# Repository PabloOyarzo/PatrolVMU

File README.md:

# PatrolVMU
Vehicle Monitoring Unit

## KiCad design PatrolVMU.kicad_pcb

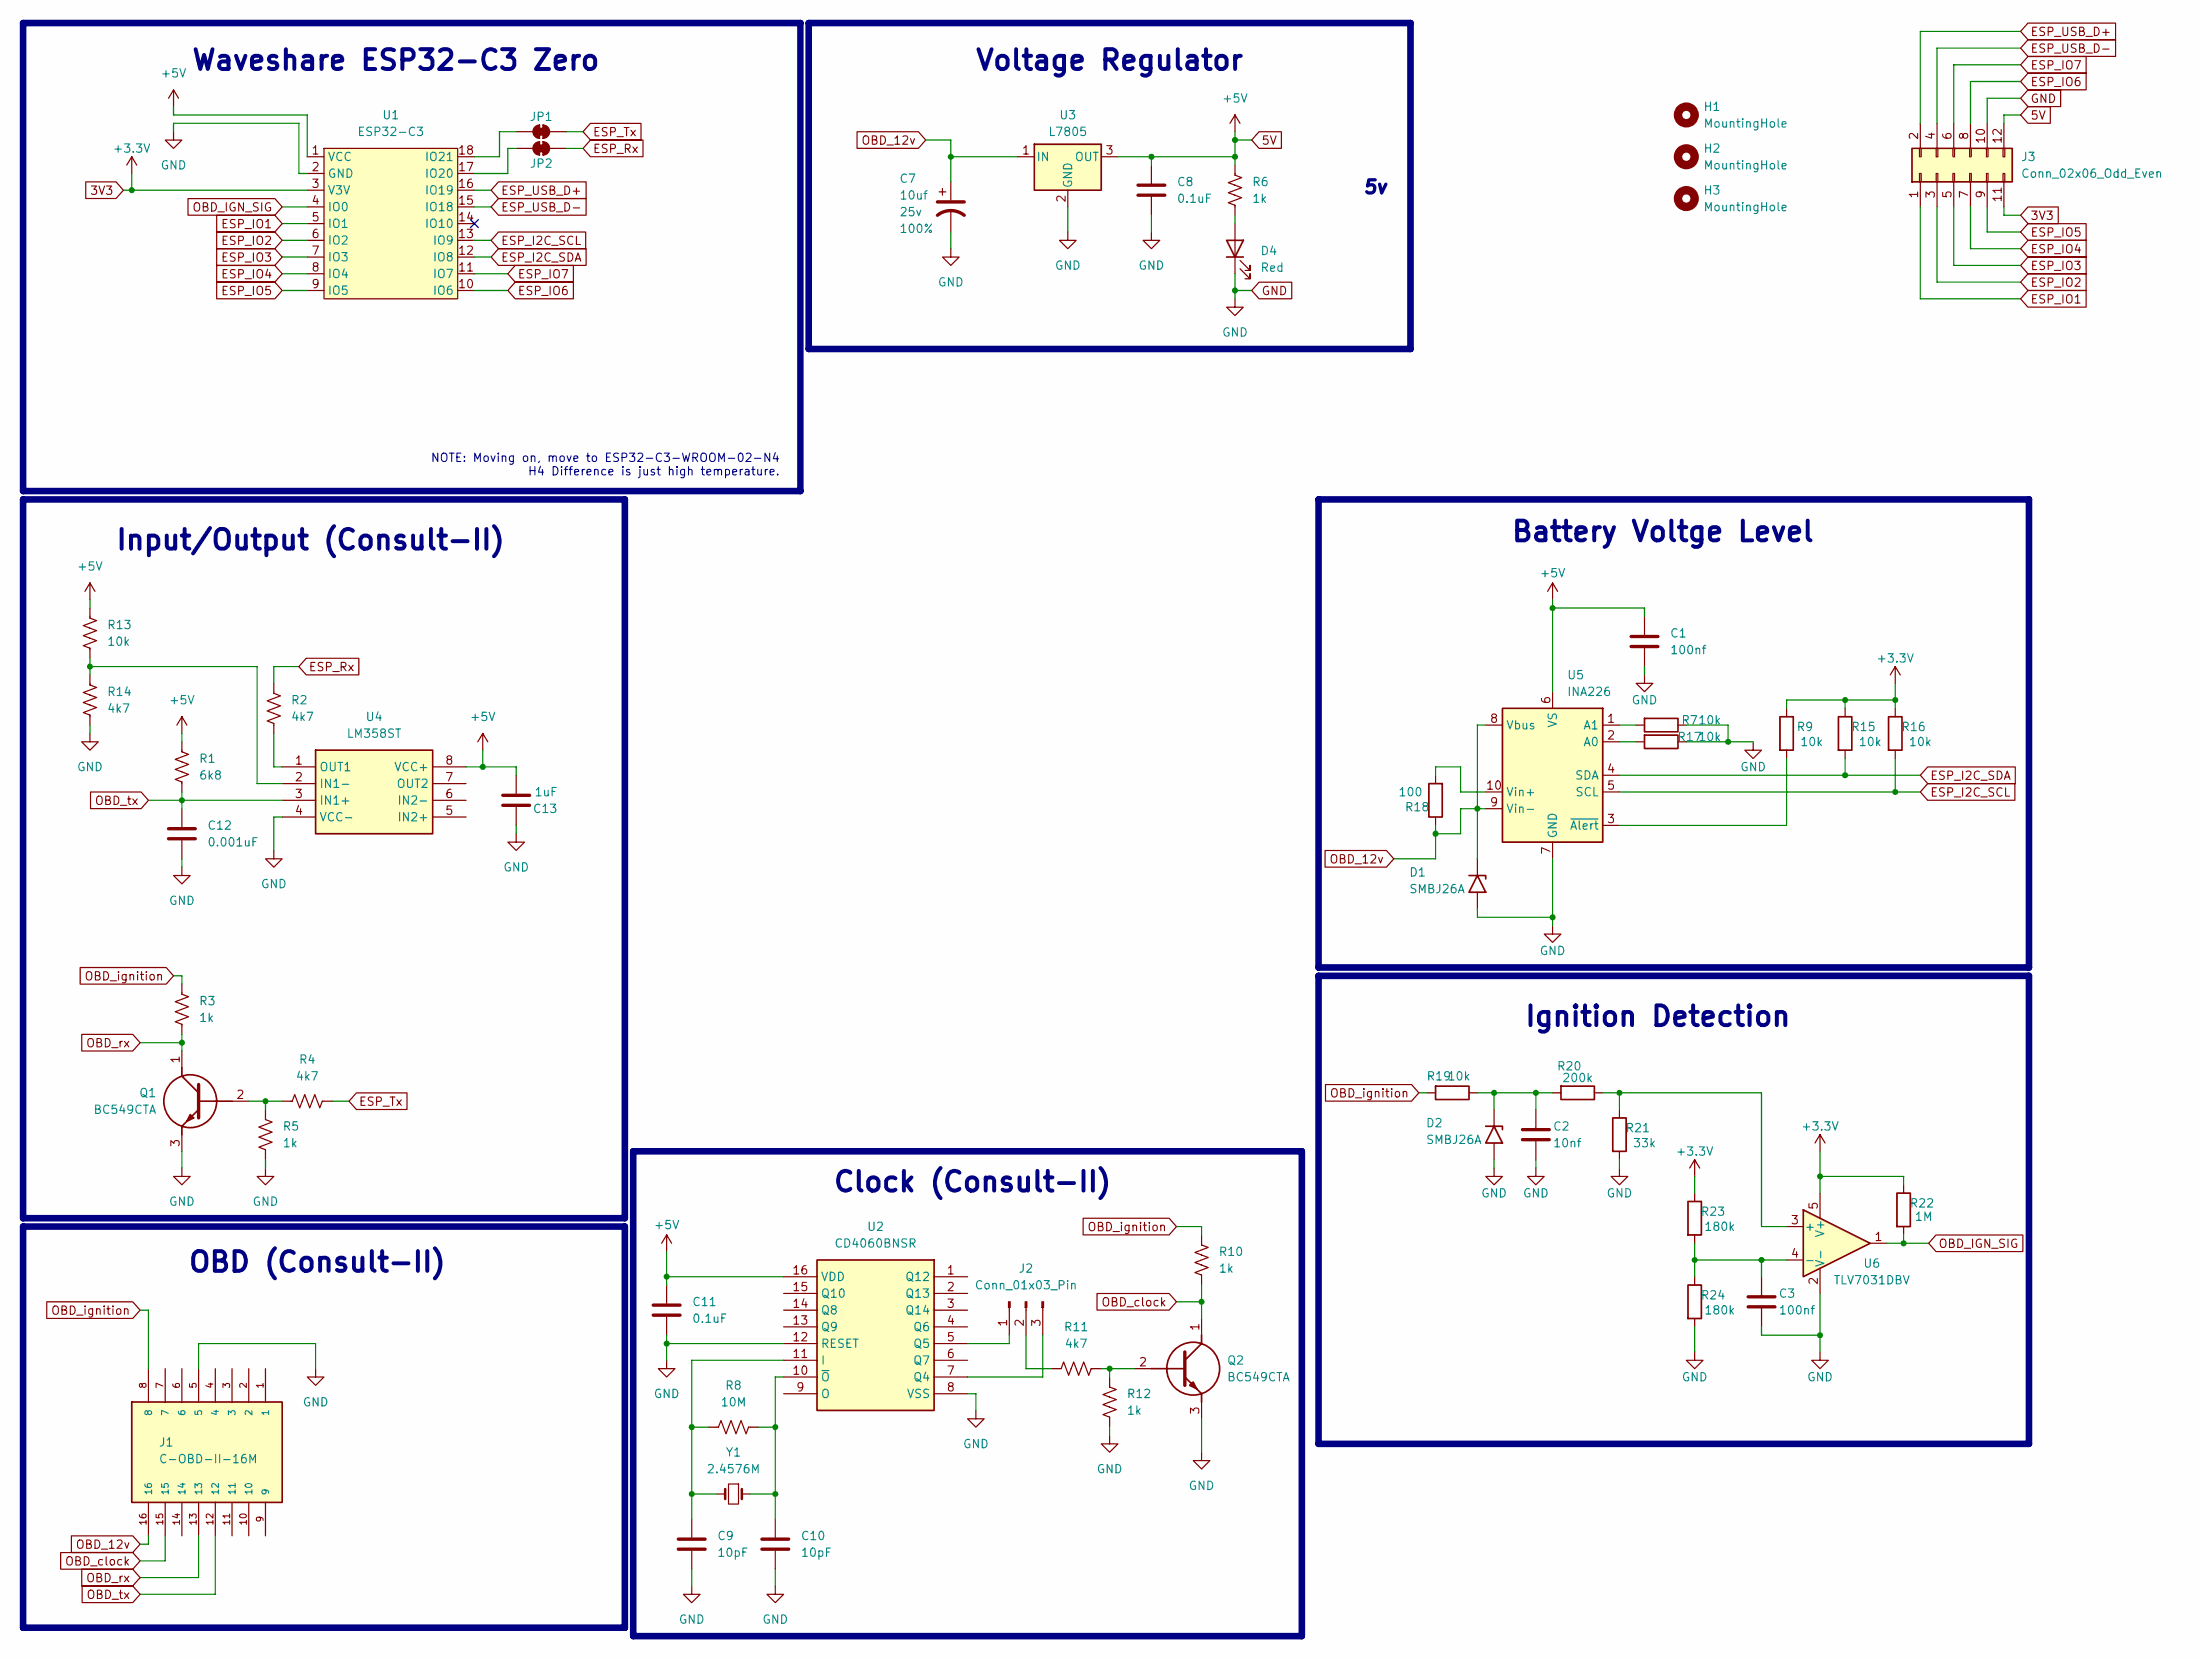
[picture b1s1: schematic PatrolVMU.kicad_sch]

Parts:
C1, C3: 100nf; C_0805_2012Metric
C2: 10nf; C_0805_2012Metric
C7: 10uf; C_0805_2012Metric; Voltage 25v; Tolerance 100%
C8, C11: 0.1uF; C_0805_2012Metric
C9, C10: 10pF; C_0805_2012Metric
C12: 0.001uF; C_0805_2012Metric
C13: 1uF; C_0805_2012Metric
D1, D2: SMBJ26A; D_SMB
D4: Red; LED_0805_2012Metric
H1, H2, H3: MountingHole; MountingHole_2.2mm_M2
J1: C-OBD-II-16M; COMTECH_C-OBD-II-16M; PARTREV A
J2: Conn_01x03_Pin; SolderJumper-3_P1.3mm_Bridged2Bar12_Pad1.0x1.5mm
J3: Conn_02x06_Odd_Even; PinHeader_2x06_P2.54mm_Vertical
JP1, JP2: SolderJumper_2_Bridged; SolderJumper-2_P1.3mm_Bridged2Bar_Pad1.0x1.5mm
Q1, Q2: BC549CTA; BC33740TA; Mouser Part Number 512-BC549CTA
R1: 6k8; C_0805_2012Metric
R2, R4, R11, R14: 4k7; C_0805_2012Metric
R3, R5, R6, R10, R12: 1k; C_0805_2012Metric
R7, R9, R13, R15, R16, R17, R19: 10k; C_0805_2012Metric
R8: 10M; C_0805_2012Metric
R18: 100; R_2512_6332Metric
R20: 200k; C_0805_2012Metric
R21: 33k; C_0805_2012Metric
R22: 1M; C_0805_2012Metric
R23, R24: 180k; C_0805_2012Metric
U1: ESP32-C3; Waveshare-ESP32-C3-Zero
U2: CD4060BNSR; SOIC127P780X200-16N; Mouser Part Number 595-CD4060BNSR
U3: L7805; TO-263-2
U4: LM358ST; SOP65P490X110-8N; Mouser Part Number 511-LM358S
U5: INA226; VSSOP-10_3x3mm_P0.5mm
U6: TLV7031DBV; SOT-23-5
Y1: 2.4576M; Crystal_HC49-4H_Vertical

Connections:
3V3: J3.11, R9.1, R15.1, R16.1, R22.1, R23.1, U1.3 (V3V), U6.5 (V+)
5V: C1.1, C8.1, C11.1, C13.2, J3.12, R1.1, R6.1, R13.1, U1.1 (VCC), U2.16 (VDD), U3.3 (OUT), U4.8 (VCC+), U5.6 (VS)
ESP_I2C_SCL: R16.2, U1.13 (IO9), U5.5 (SCL)
ESP_I2C_SDA: R15.2, U1.12 (IO8), U5.4 (SDA)
ESP_IO1: J3.1, U1.5 (IO1)
ESP_IO2: J3.3, U1.6 (IO2)
ESP_IO3: J3.5, U1.7 (IO3)
ESP_IO4: J3.7, U1.8 (IO4)
ESP_IO5: J3.9, U1.9 (IO5)
ESP_IO6: J3.8, U1.10 (IO6)
ESP_IO7: J3.6, U1.11 (IO7)
ESP_Rx: JP2.2 (B), R2.1
ESP_Tx: JP1.2 (B), R4.2
ESP_USB_D+: J3.2, U1.16 (IO19)
ESP_USB_D-: J3.4, U1.15 (IO18)
GND: C1.2, C2.2, C3.2, C7.2, C8.2, C9.2, C10.2, C11.2, C12.2, C13.1, D1.2 (A2), D2.2 (A2), D4.1 (K), J1.5, J3.10, Q1.3 (E), Q2.3 (E), R5.2, R7.1, R12.2, R14.2, R17.1, R21.2, R24.2, U1.2 (GND), U2.8 (VSS), U2.12 (RESET), U3.2 (GND), U4.4 (VCC-), U5.7 (GND), U6.2 (V-)
unnamed: C2.1, D2.1 (A1), R19.1, R20.2
unnamed: D4.2 (A), R6.2
unnamed: J2.1, U2.5 (Q5)
unnamed: J2.2, R11.1
unnamed: J2.3, U2.7 (Q4)
unnamed: JP1.1 (A), U1.18 (IO21)
unnamed: JP2.1 (A), U1.17 (IO20)
unnamed: Q1.2 (B), R4.1, R5.1
unnamed: Q2.2 (B), R11.2, R12.1
unnamed: C9.1, R8.2, U2.11 (I), Y1.2
unnamed: C10.1, R8.1, U2.10 (~O), Y1.1
unnamed: R13.2, R14.1, U4.2 (IN1-)
unnamed: R2.2, U4.1 (OUT1)
unnamed: R17.2, U5.2 (A0)
unnamed: R7.2, U5.1 (A1)
unnamed: R18.2, U5.10 (Vin+)
unnamed: R9.2, U5.3 (~Alert)
unnamed: R20.1, R21.1, U6.3 (+)
unnamed: C3.1, R23.2, R24.1, U6.4 (-)
OBD_12v: C7.1, D1.1 (A1), J1.16, R18.1, U3.1 (IN), U5.8 (Vbus), U5.9 (Vin-)
OBD_IGN_SIG: R22.2, U1.4 (IO0), U6.1
OBD_clock: J1.15, Q2.1 (C), R10.2
OBD_ignition: J1.8, R3.1, R10.1, R19.2
OBD_rx: J1.13, Q1.1 (C), R3.2
OBD_tx: C12.1, J1.12, R1.2, U4.3 (IN1+)

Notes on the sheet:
OBD (Consult-II)
Clock (Consult-II)
Battery Voltge Level
NOTE: Moving on, move to ESP32-C3-WROOM-02-N4 H4 Difference is just high temperature.
Waveshare ESP32-C3 Zero
Voltage Regulator
Input/Output (Consult-II)
Ignition Detection

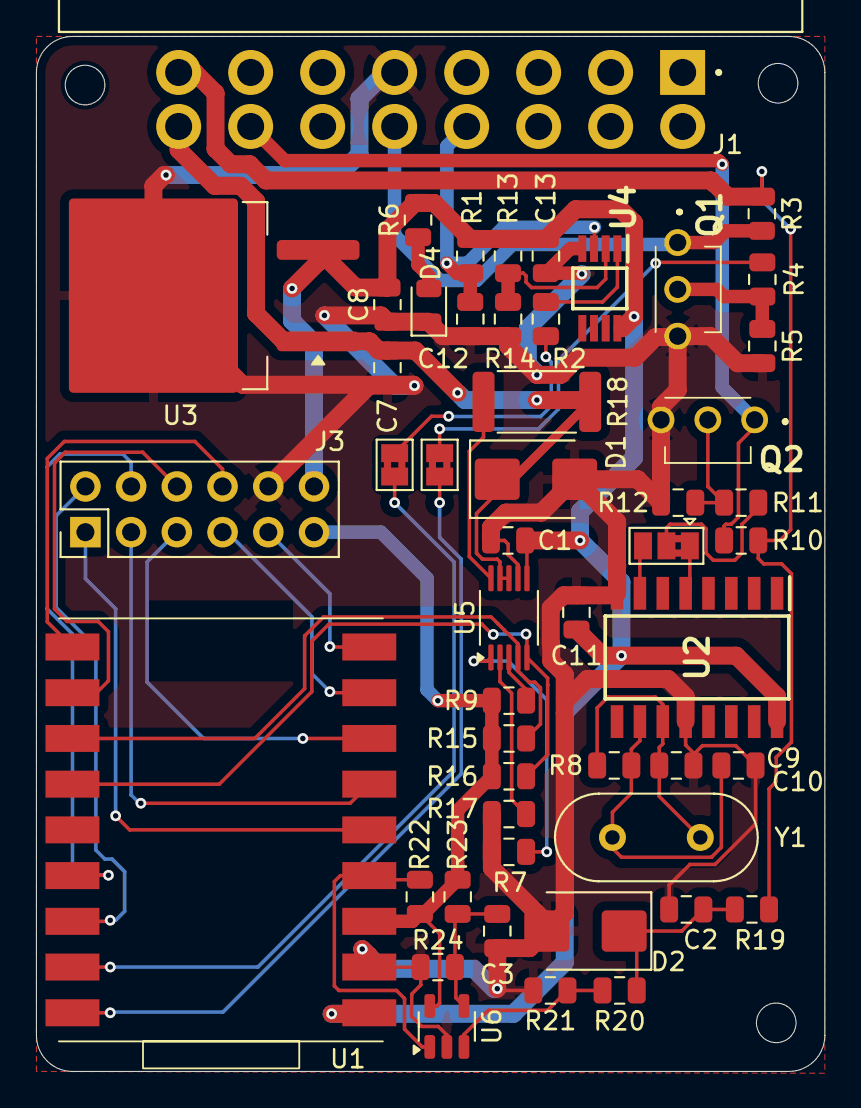
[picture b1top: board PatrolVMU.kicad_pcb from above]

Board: 2 copper layers, 43.8 x 57.5 mm, 54 parts (0 on the bottom side), 41 nets.

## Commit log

2024-04-09 did most of the schematic
2024-04-15 added Lead Acid Monitor IC
2025-08-16 making provisional connector
2025-08-17 finished preliminarly
2025-09-29 fixed texts, added mt holes, etc
